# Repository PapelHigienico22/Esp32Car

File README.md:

Librerias:

PS3:
https://www.arduino.cc/reference/en/libraries/ps3-controller-host/

Servo:
https://www.arduino.cc/reference/en/libraries/esp32servo/

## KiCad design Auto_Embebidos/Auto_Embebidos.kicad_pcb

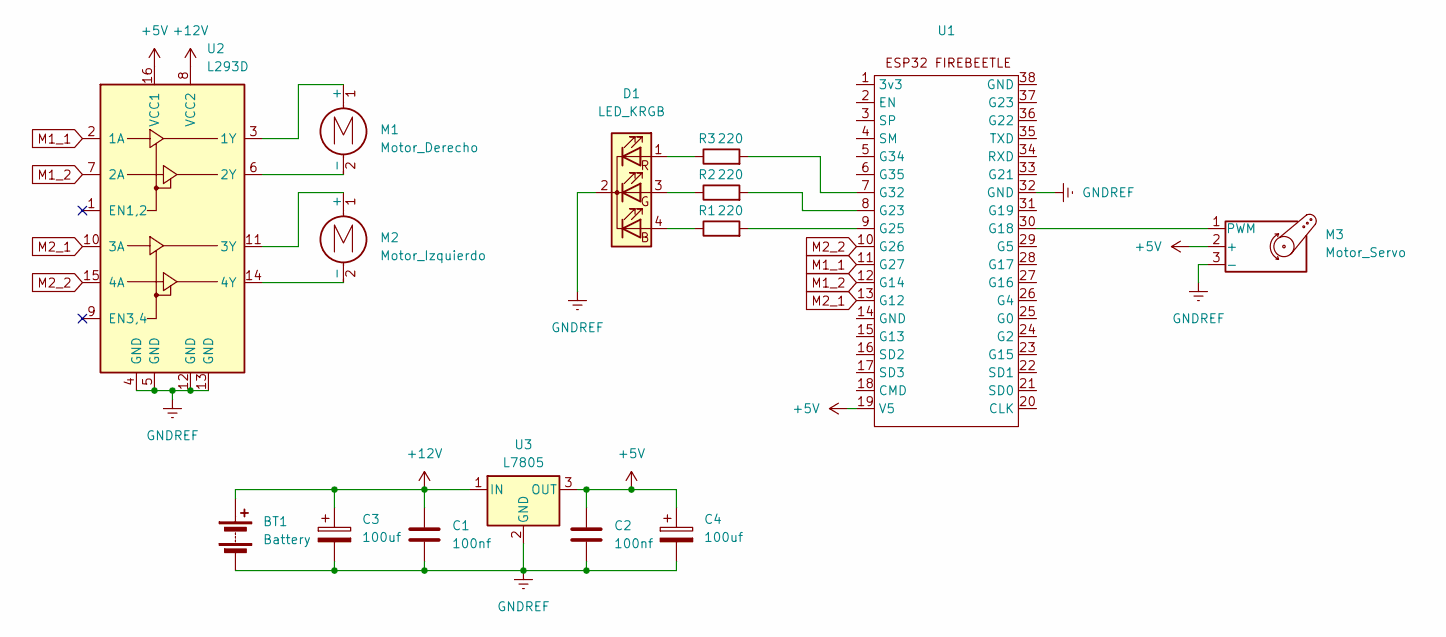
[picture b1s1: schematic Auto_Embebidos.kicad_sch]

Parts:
BT1: Battery; PinHeader_1x02_P2.54mm_Vertical
C1, C2: 100nf; C_Disc_D5.0mm_W2.5mm_P5.00mm
C3, C4: 100uf; CP_Radial_D5.0mm_P2.50mm
D1: LED_KRGB; LED_D5.0mm-4_RGB_Wide_Pins
M1: Motor_Derecho; TerminalBlock_MetzConnect_Type011_RT05502HBWC_1x02_P5.00mm_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
M2: Motor_Izquierdo; TerminalBlock_MetzConnect_Type011_RT05502HBWC_1x02_P5.00mm_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
M3: Motor_Servo; PinHeader_1x03_P2.54mm_Vertical
R1, R2, R3: 220; R_Axial_DIN0204_L3.6mm_D1.6mm_P7.62mm_Horizontal
U1: firebeetle
U2: L293D; DIP-16_W7.62mm
U3: L7805; TO-220-3_Horizontal_TabUp

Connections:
+5V: C2.1, C4.1, M3.2 (+), U1.19 (V5), U2.16 (VCC1), U3.3 (OUT)
+12V: BT1.1 (+), C1.1, C3.1, U2.8 (VCC2), U3.1 (IN)
GNDREF: BT1.2 (-), C1.2, C2.2, C3.2, C4.2, D1.2 (K), M3.3 (-), U1.32 (GND), U2.4 (GND), U2.5 (GND), U2.12 (GND), U2.13 (GND), U3.2 (GND)
M1_1: U1.11 (G27), U2.2 (1A)
M1_2: U1.12 (G14), U2.7 (2A)
M2_1: U1.13 (G12), U2.10 (3A)
M2_2: U1.10 (G26), U2.15 (4A)
unnamed: D1.4 (BA), R1.1
unnamed: D1.3 (GA), R2.1
unnamed: D1.1 (RA), R3.1
unnamed: M1.1 (+), U2.3 (1Y)
unnamed: M1.2 (-), U2.6 (2Y)
unnamed: M2.1 (+), U2.11 (3Y)
unnamed: M2.2 (-), U2.14 (4Y)
unnamed: M3.1 (PWM), U1.30 (G18)
unnamed: R2.2, U1.8 (G23)
unnamed: R1.2, U1.9 (G25)
unnamed: R3.2, U1.7 (G32)

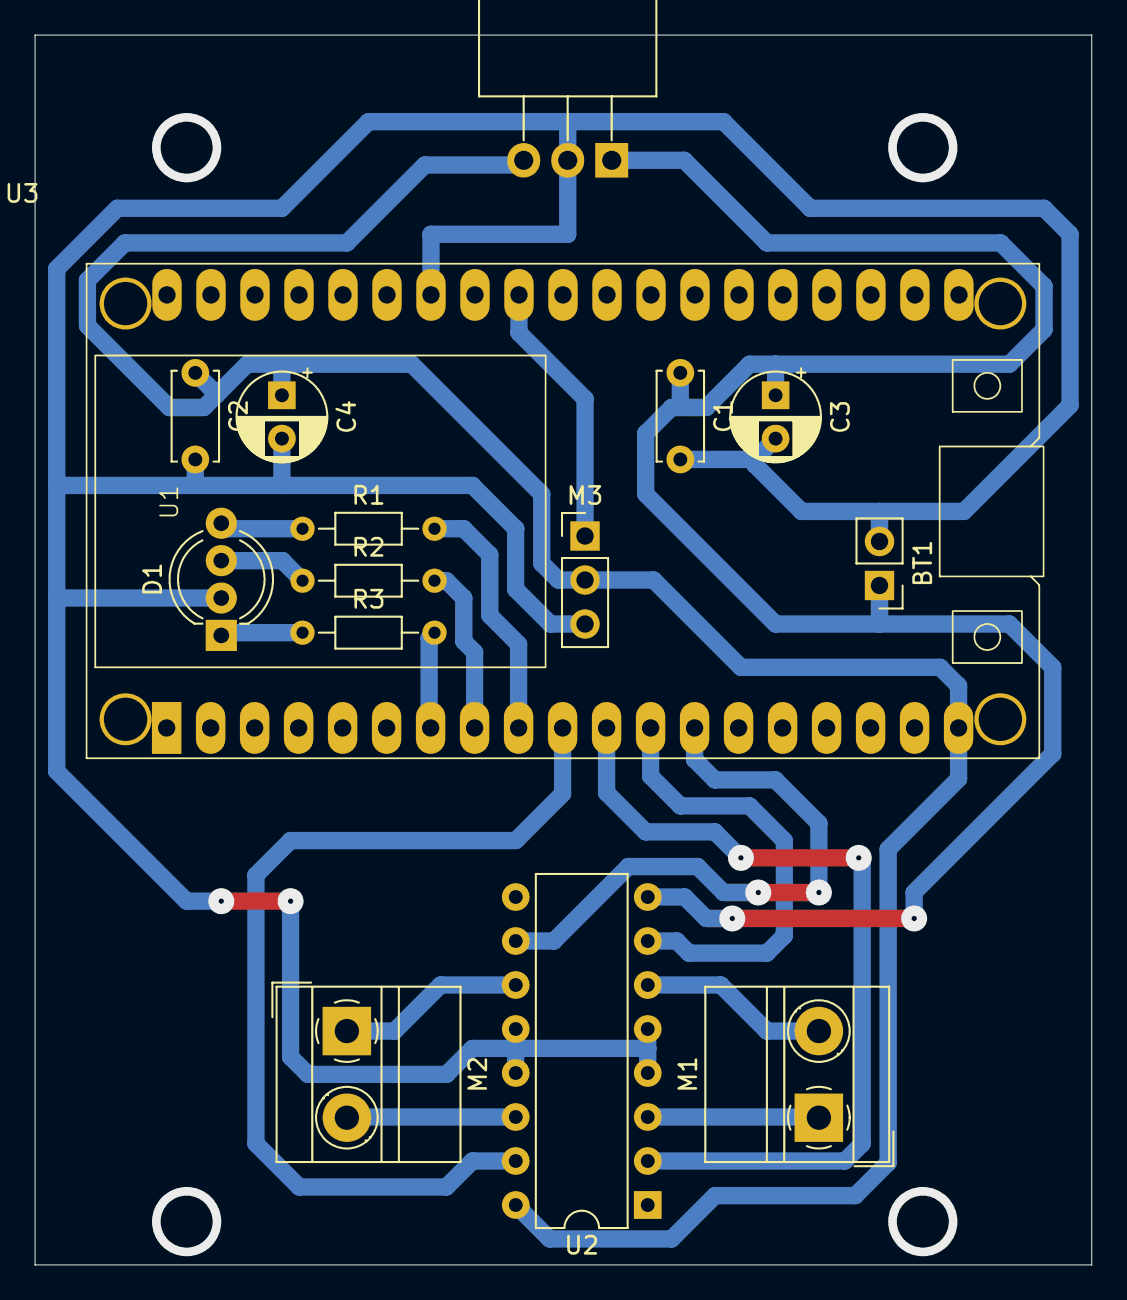
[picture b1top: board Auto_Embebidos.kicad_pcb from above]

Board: 2 copper layers, 61.0 x 71.0 mm, 15 parts (0 on the bottom side), 18 nets.

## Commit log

2024-07-10 Add files via upload
    Le añadí nitro al codigo
2024-09-18 actualizacion vistosa
    Actualicé la logica relativa con la funcion ledc, agregué un buzzer y un led rgb
